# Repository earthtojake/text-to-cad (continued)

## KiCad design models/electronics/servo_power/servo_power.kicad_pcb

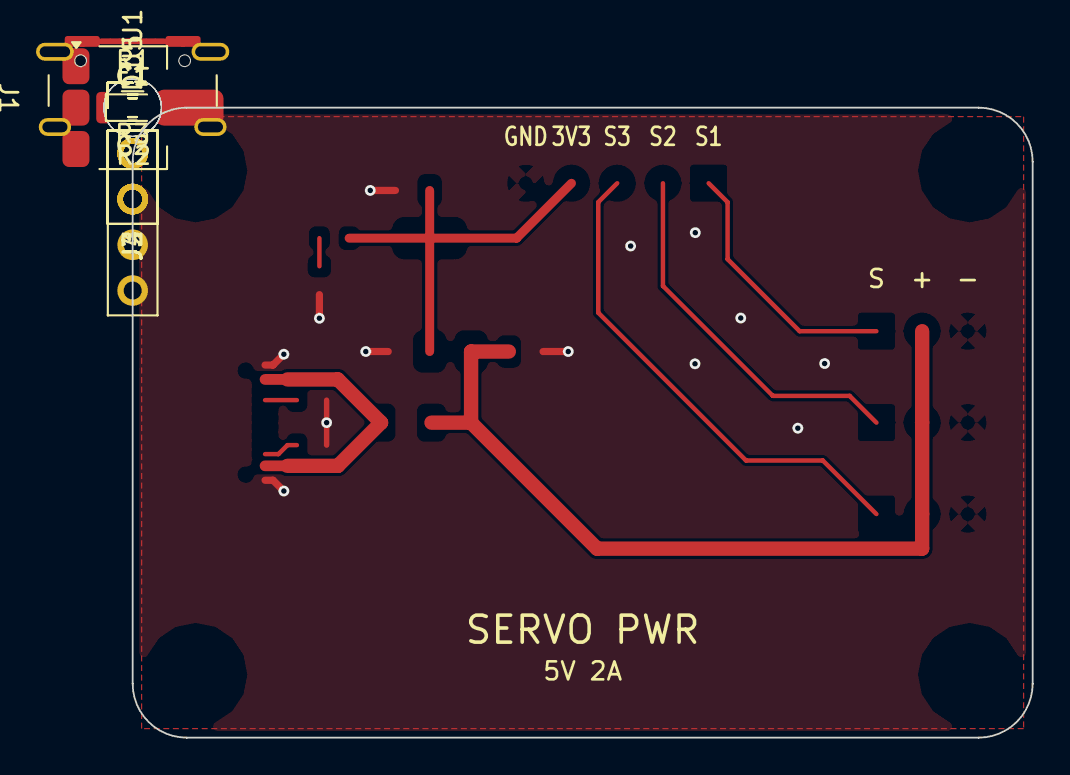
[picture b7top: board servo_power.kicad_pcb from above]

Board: 2 copper layers, 50.0 x 35.0 mm, 17 parts (0 on the bottom side), 10 nets.

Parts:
C1: 10uF; C_0805_2012Metric
C2: 22uF; C_0805_2012Metric
D1: green; LED_0603_1608Metric
F1: 2A polyfuse; Fuse_1206_3216Metric
H1, H2, H3, H4: M3; MountingHole_3.2mm_M3
J1: USB4105-GF-A; USB_C_Receptacle_GCT_USB4105-xx-A_16P_TopMnt_Horizontal
J2: servo 1; PinHeader_1x03_P2.54mm_Vertical
J3: servo 2; PinHeader_1x03_P2.54mm_Vertical
J4: servo 3; PinHeader_1x03_P2.54mm_Vertical
J5: logic; PinHeader_1x05_P2.54mm_Vertical
R1, R2: 5.1k; R_0603_1608Metric
R3: 1k; R_0603_1608Metric
U1: AMS1117-3.3; SOT-223-3_TabPin2

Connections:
+3V3: C2.1, J5.4, R3.1, U1.2
+5V: C1.1, F1.2, J2.2, J3.2, J4.2, U1.3
CC1: J1.A5, R1.1
CC2: J1.B5, R2.1
GND: C1.2, C2.2, D1.1, J1.A1, J1.A12, J1.B1, J1.B12, J1.SH, J2.3, J3.3, J4.3, J5.5, R1.2, R2.2, U1.1
LED: D1.2, R3.2
S1: J2.1, J5.1
S2: J3.1, J5.2
S3: J4.1, J5.3
VBUS: F1.1, J1.A4, J1.A9, J1.B4, J1.B9

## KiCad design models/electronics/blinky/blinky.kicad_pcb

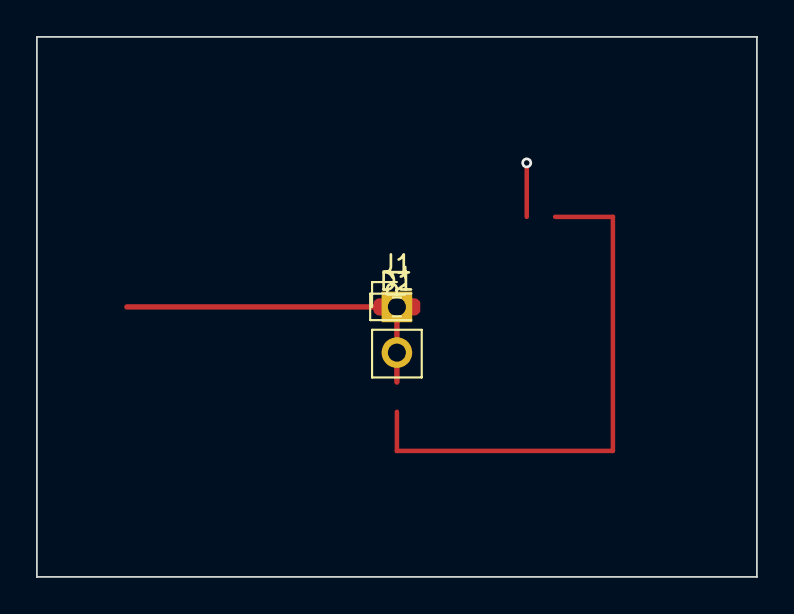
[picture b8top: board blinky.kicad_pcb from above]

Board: 2 copper layers, 40.0 x 30.0 mm, 3 parts (0 on the bottom side), 3 nets.

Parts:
D1: LED_0603_1608Metric
J1: PinHeader_1x02_P2.54mm_Vertical
R1: R_0603_1608Metric

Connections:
GND: D1.1, J1.2
LED: D1.2, R1.2
VBUS: J1.1, R1.1
